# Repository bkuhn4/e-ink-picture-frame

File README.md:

# e-ink-picture-frame

## Getting started

To make it easy for you to get started with GitLab, here's a list of recommended next steps.

Already a pro? Just edit this README.md and make it your own. Want to make it easy? [Use the template at the bottom](#editing-this-readme)!

## Add your files

- [ ] [Create](https://docs.gitlab.com/ee/user/project/repository/web_editor.html#create-a-file) or [upload](https://docs.gitlab.com/ee/user/project/repository/web_editor.html#upload-a-file) files
- [ ] [Add files using the command line](https://docs.gitlab.com/topics/git/add_files/#add-files-to-a-git-repository) or push an existing Git repository with the following command:

```
cd existing_repo
git remote add origin https://git.ece.iastate.edu/etg_dev/cpre_488_pcam.git
git branch -M main
git push -uf origin main
```

## Integrate with your tools

- [ ] [Set up project integrations](https://git.ece.iastate.edu/etg_dev/cpre_488_pcam/-/settings/integrations)

## Collaborate with your team

- [ ] [Invite team members and collaborators](https://docs.gitlab.com/ee/user/project/members/)
- [ ] [Create a new merge request](https://docs.gitlab.com/ee/user/project/merge_requests/creating_merge_requests.html)
- [ ] [Automatically close issues from merge requests](https://docs.gitlab.com/ee/user/project/issues/managing_issues.html#closing-issues-automatically)
- [ ] [Enable merge request approvals](https://docs.gitlab.com/ee/user/project/merge_requests/approvals/)
- [ ] [Set auto-merge](https://docs.gitlab.com/user/project/merge_requests/auto_merge/)

## Test and Deploy

Use the built-in continuous integration in GitLab.

- [ ] [Get started with GitLab CI/CD](https://docs.gitlab.com/ee/ci/quick_start/)
- [ ] [Analyze your code for known vulnerabilities with Static Application Security Testing (SAST)](https://docs.gitlab.com/ee/user/application_security/sast/)
- [ ] [Deploy to Kubernetes, Amazon EC2, or Amazon ECS using Auto Deploy](https://docs.gitlab.com/ee/topics/autodevops/requirements.html)
- [ ] [Use pull-based deployments for improved Kubernetes management](https://docs.gitlab.com/ee/user/clusters/agent/)
- [ ] [Set up protected environments](https://docs.gitlab.com/ee/ci/environments/protected_environments.html)

***

# Editing this README

When you're ready to make this README your own, just edit this file and use the handy template below (or feel free to structure it however you want - this is just a starting point!). Thanks to [makeareadme.com](https://www.makeareadme.com/) for this template.

## Suggestions for a good README

Every project is different, so consider which of these sections apply to yours. The sections used in the template are suggestions for most open source projects. Also keep in mind that while a README can be too long and detailed, too long is better than too short. If you think your README is too long, consider utilizing another form of documentation rather than cutting out information.

## Name
Choose a self-explaining name for your project.

## Description
Let people know what your project can do specifically. Provide context and add a link to any reference visitors might be unfamiliar with. A list of Features or a Background subsection can also be added here. If there are alternatives to your project, this is a good place to list differentiating factors.

## Badges
On some READMEs, you may see small images that convey metadata, such as whether or not all the tests are passing for the project. You can use Shields to add some to your README. Many services also have instructions for adding a badge.

## Visuals
Depending on what you are making, it can be a good idea to include screenshots or even a video (you'll frequently see GIFs rather than actual videos). Tools like ttygif can help, but check out Asciinema for a more sophisticated method.

## Installation
Within a particular ecosystem, there may be a common way of installing things, such as using Yarn, NuGet, or Homebrew. However, consider the possibility that whoever is reading your README is a novice and would like more guidance. Listing specific steps helps remove ambiguity and gets people to using your project as quickly as possible. If it only runs in a specific context like a particular programming language version or operating system or has dependencies that have to be installed manually, also add a Requirements subsection.

## Usage
Use examples liberally, and show the expected output if you can. It's helpful to have inline the smallest example of usage that you can demonstrate, while providing links to more sophisticated examples if they are too long to reasonably include in the README.

## Support
Tell people where they can go to for help. It can be any combination of an issue tracker, a chat room, an email address, etc.

## Roadmap
If you have ideas for releases in the future, it is a good idea to list them in the README.

## Contributing
State if you are open to contributions and what your requirements are for accepting them.

For people who want to make changes to your project, it's helpful to have some documentation on how to get started. Perhaps there is a script that they should run or some environment variables that they need to set. Make these steps explicit. These instructions could also be useful to your future self.

You can also document commands to lint the code or run tests. These steps help to ensure high code quality and reduce the likelihood that the changes inadvertently break something. Having instructions for running tests is especially helpful if it requires external setup, such as starting a Selenium server for testing in a browser.

## Authors and acknowledgment
Show your appreciation to those who have contributed to the project.

## License
For open source projects, say how it is licensed.

## Project status
If you have run out of energy or time for your project, put a note at the top of the README saying that development has slowed down or stopped completely. Someone may choose to fork your project or volunteer to step in as a maintainer or owner, allowing your project to keep going. You can also make an explicit request for maintainers.

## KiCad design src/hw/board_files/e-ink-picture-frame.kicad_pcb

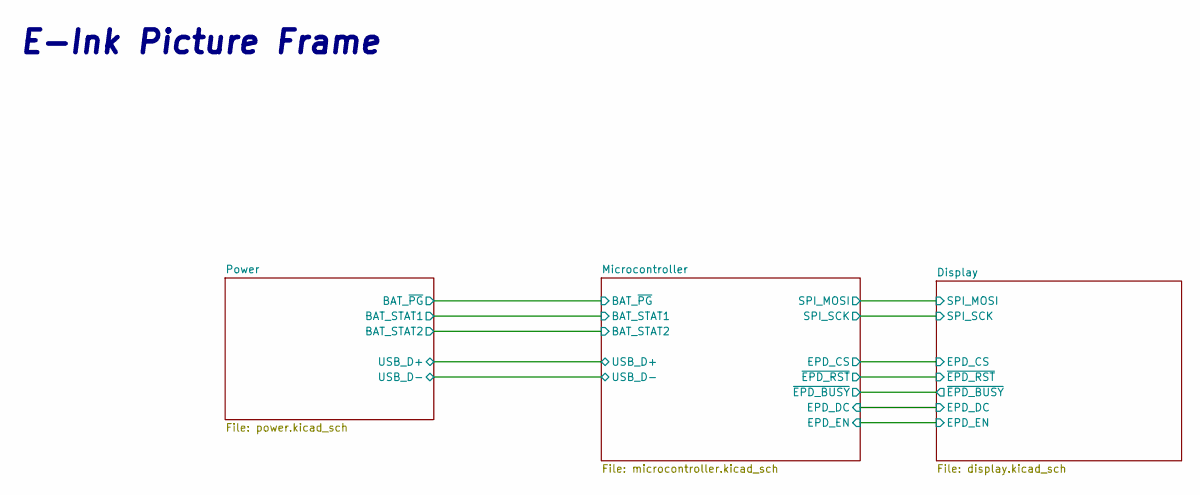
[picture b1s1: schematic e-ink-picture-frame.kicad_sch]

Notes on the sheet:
E-Ink Picture Frame

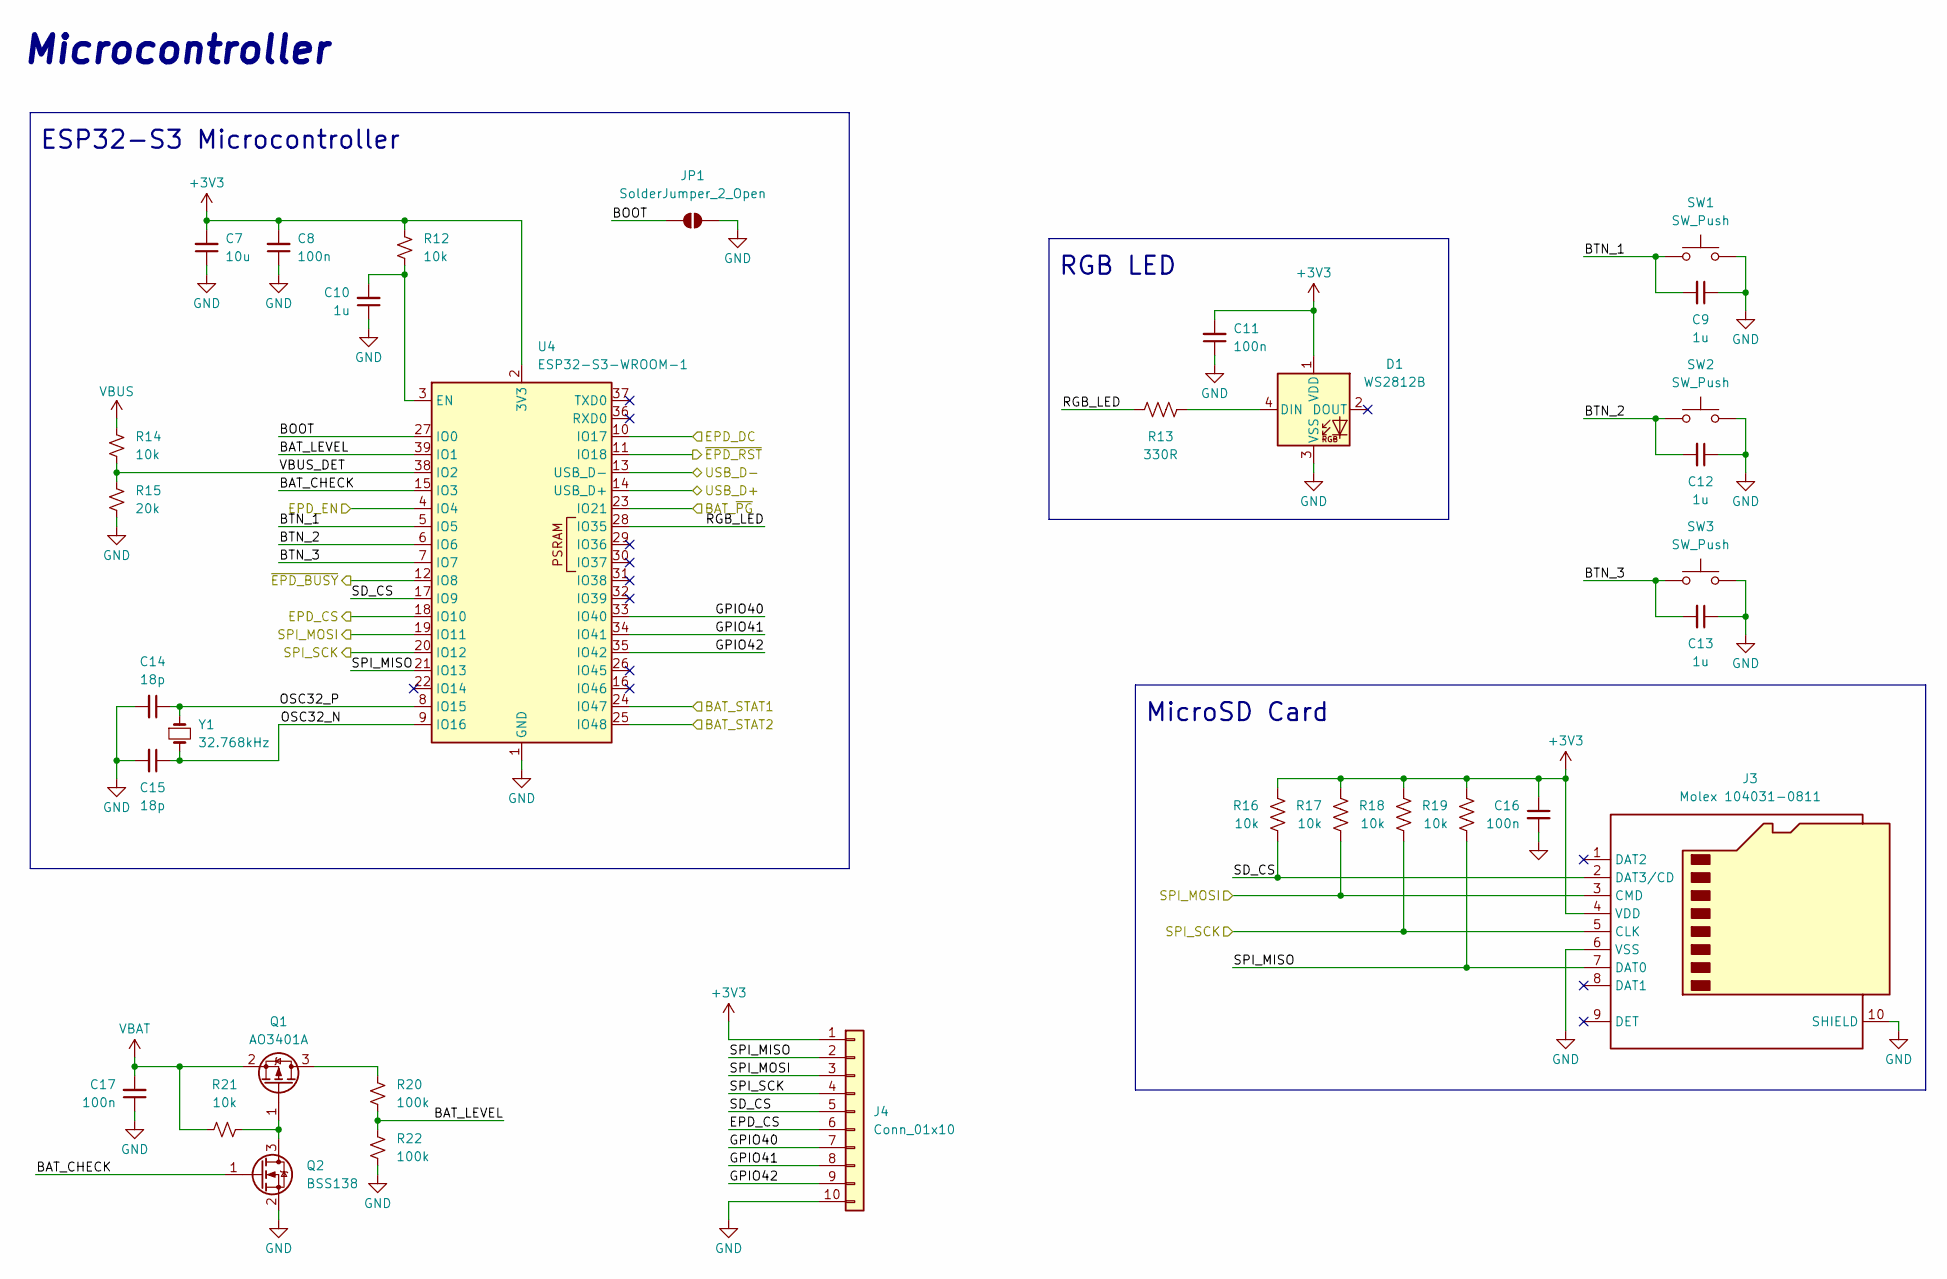
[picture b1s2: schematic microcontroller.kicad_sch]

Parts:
C7: 10u; C_0805_2012Metric_Pad1.18x1.45mm_HandSolder
C8, C11, C16, C17: 100n; C_0603_1608Metric_Pad1.08x0.95mm_HandSolder
C9, C10, C12, C13: 1u; C_0603_1608Metric_Pad1.08x0.95mm_HandSolder
C14, C15: 18p; C_0603_1608Metric_Pad1.08x0.95mm_HandSolder
D1: WS2812B; LED_WS2812B_PLCC4_5.0x5.0mm_P3.2mm
J3: Molex 104031-0811; microSD_HC_Hirose_DM3D-SF
J4: Conn_01x10; PinSocket_1x10_P2.54mm_Horizontal
JP1: SolderJumper_2_Open; SolderJumper-2_P1.3mm_Open_RoundedPad1.0x1.5mm
Q1: AO3401A; SOT-23
Q2: BSS138; SOT-23
R12, R14, R16, R17, R18, R19, R21: 10k; R_0603_1608Metric_Pad0.98x0.95mm_HandSolder
R13: 330R; R_0603_1608Metric_Pad0.98x0.95mm_HandSolder
R15: 20k; R_0603_1608Metric_Pad0.98x0.95mm_HandSolder
R20, R22: 100k; R_0805_2012Metric_Pad1.20x1.40mm_HandSolder
SW1, SW2, SW3: SW_Push; SW_PUSH_6mm
U4: ESP32-S3-WROOM-1
Y1: 32.768kHz; Crystal_SMD_3215-2Pin_3.2x1.5mm

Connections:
+3V3: C7.2, C8.2, C11.2, C16.1, D1.1 (VDD), J3.4 (VDD), J4.1, R12.1, R16.1, R17.1, R18.1, R19.1, U4.2 (3V3); also elsewhere on the board
/Display/EPD_DC: U4.10 (IO17); also elsewhere on the board
/Display/EPD_EN: U4.4 (IO4); also elsewhere on the board
/Display/~EPD_BUSY: U4.12 (IO8); also elsewhere on the board
/Display/~EPD_RST: U4.11 (IO18); also elsewhere on the board
/Microcontroller/BAT_CHECK: Q2.1 (G), U4.15 (IO3)
/Microcontroller/BAT_LEVEL: R20.2, R22.1, U4.39 (IO1)
/Microcontroller/BAT_STAT1: U4.24 (IO47); also elsewhere on the board
/Microcontroller/BAT_STAT2: U4.25 (IO48); also elsewhere on the board
/Microcontroller/BAT_~PG: U4.23 (IO21); also elsewhere on the board
/Microcontroller/BOOT: JP1.1 (A), U4.27 (IO0)
/Microcontroller/BTN_1: C9.2, SW1.1, U4.5 (IO5)
/Microcontroller/BTN_2: C12.2, SW2.1, U4.6 (IO6)
/Microcontroller/BTN_3: C13.2, SW3.1, U4.7 (IO7)
/Microcontroller/EPD_CS: J4.6, U4.18 (IO10); also elsewhere on the board
/Microcontroller/GPIO40: J4.7, U4.33 (IO40)
/Microcontroller/GPIO41: J4.8, U4.34 (IO41)
/Microcontroller/GPIO42: J4.9, U4.35 (IO42)
/Microcontroller/OSC32_N: C15.1, U4.9 (IO16), Y1.2
/Microcontroller/OSC32_P: C14.1, U4.8 (IO15), Y1.1
/Microcontroller/RGB_LED: R13.1, U4.28 (IO35)
/Microcontroller/SD_CS: J3.2 (DAT3/CD), J4.5, R16.2, U4.17 (IO9)
/Microcontroller/SPI_MISO: J3.7 (DAT0), J4.2, R19.2, U4.21 (IO13)
/Microcontroller/SPI_MOSI: J3.3 (CMD), J4.3, R17.2, U4.19 (IO11); also elsewhere on the board
/Microcontroller/SPI_SCK: J3.5 (CLK), J4.4, R18.2, U4.20 (IO12); also elsewhere on the board
/Microcontroller/USB_D+: U4.14 (USB_D+); also elsewhere on the board
/Microcontroller/USB_D-: U4.13 (USB_D-); also elsewhere on the board
/Microcontroller/VBUS_DET: R14.2, R15.1, U4.38 (IO2)
GND: C7.1, C8.1, C9.1, C10.1, C11.1, C12.1, C13.1, C14.2, C15.2, C16.2, C17.1, D1.3 (VSS), J3.6 (VSS), J3.10 (SHIELD), J4.10, JP1.2 (B), Q2.2 (S), R15.2, R22.2, SW1.2, SW2.2, SW3.2, U4.1 (GND), U4.40 (GND), U4.41 (GND); also elsewhere on the board
unnamed: D1.4 (DIN), R13.2
unnamed: Q1.3 (D), R20.1
unnamed: Q1.1 (G), Q2.3 (D), R21.2
unnamed: C10.2, R12.2, U4.3 (EN)
VBAT: C17.2, Q1.2 (S), R21.1; also elsewhere on the board
VBUS: R14.1; also elsewhere on the board

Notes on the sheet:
RGB LED
ESP32-S3 Microcontroller
MicroSD Card
Microcontroller

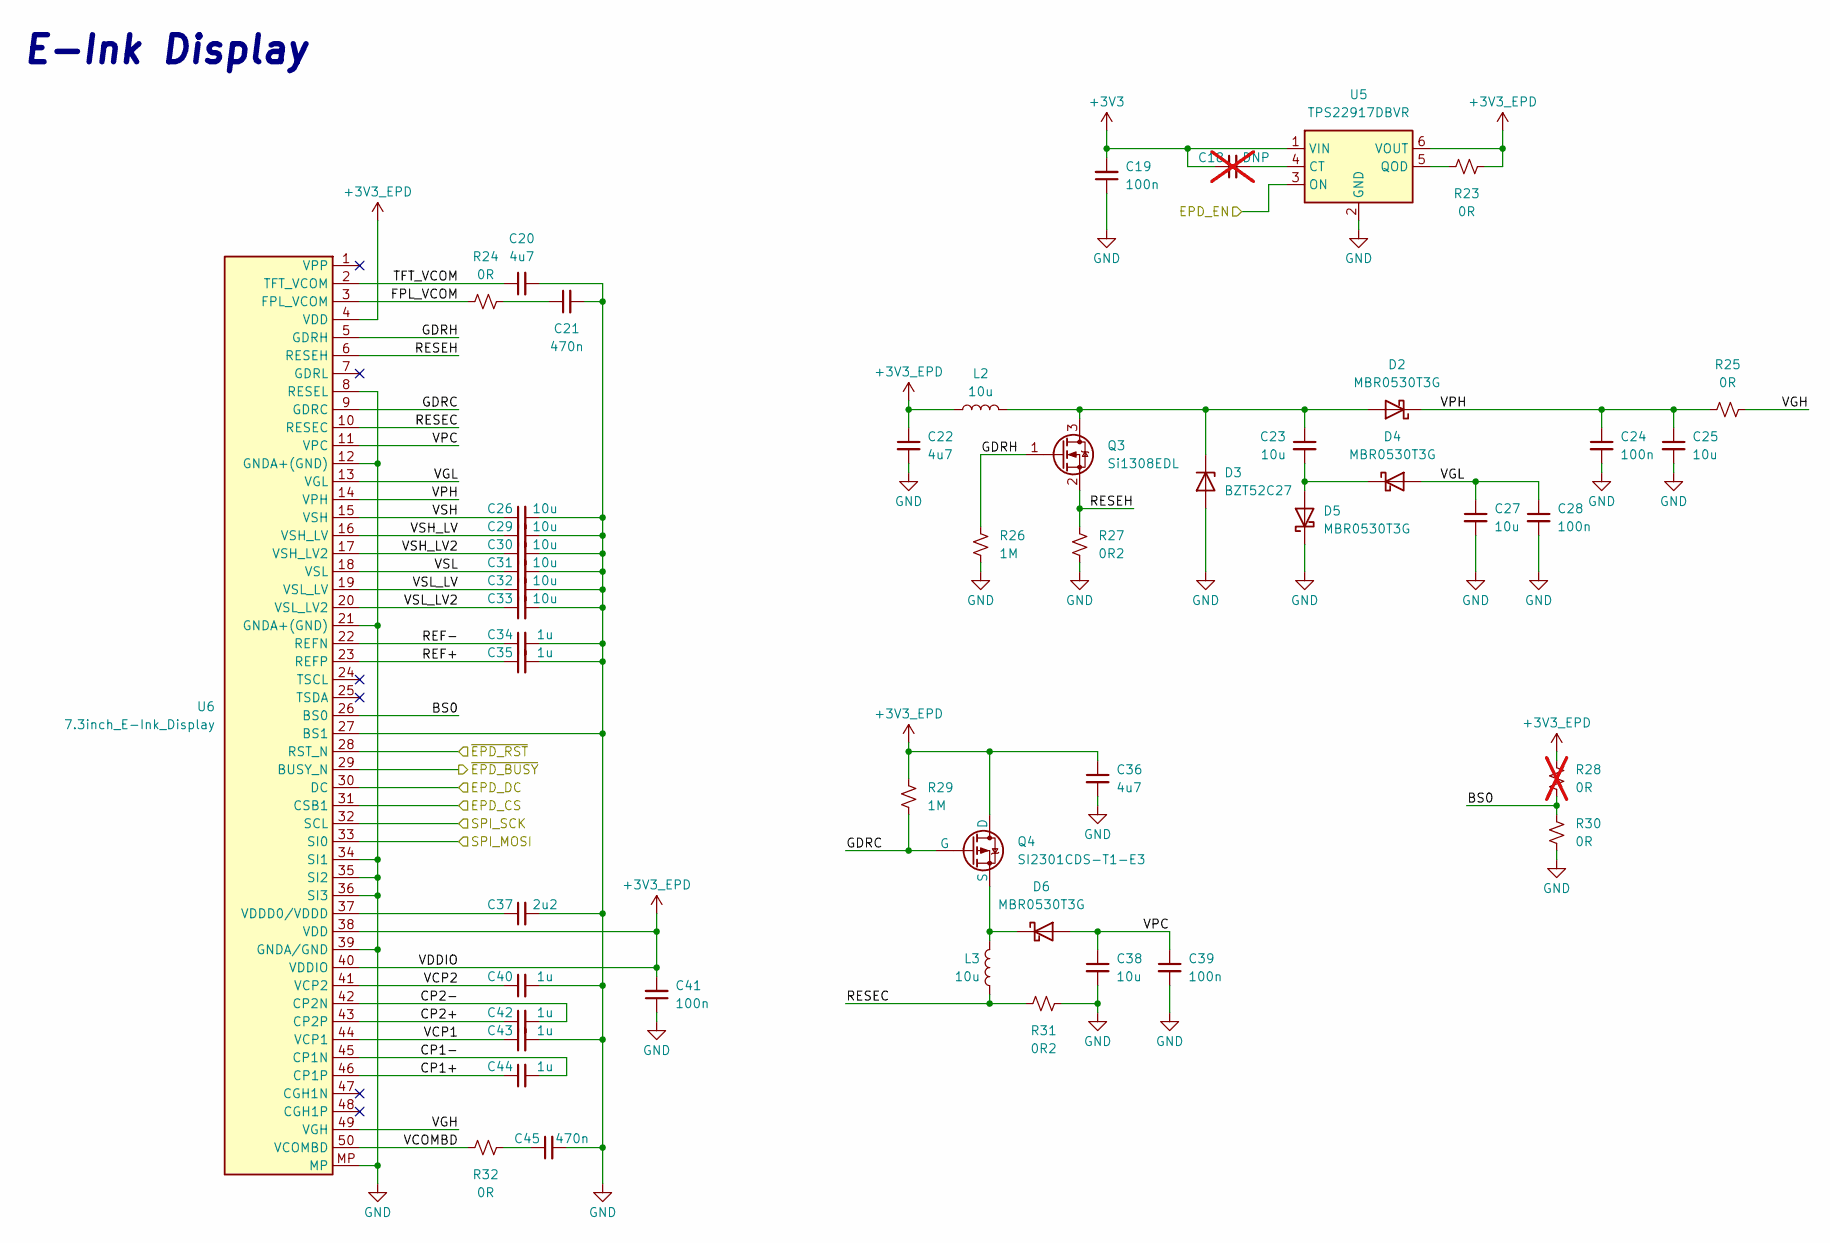
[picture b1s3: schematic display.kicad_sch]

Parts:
C18: DNP; C_0603_1608Metric_Pad1.08x0.95mm_HandSolder; not fitted
C19, C24, C28, C39, C41: 100n; C_0603_1608Metric_Pad1.08x0.95mm_HandSolder
C20, C22, C36: 4u7; C_0805_2012Metric_Pad1.18x1.45mm_HandSolder
C21, C45: 470n; C_0603_1608Metric_Pad1.08x0.95mm_HandSolder
C23, C25, C26, C27, C29, C30, C31, C32, C33, C38: 10u; C_0805_2012Metric_Pad1.18x1.45mm_HandSolder
C34, C35, C40, C42, C43, C44: 1u; C_0603_1608Metric_Pad1.08x0.95mm_HandSolder
C37: 2u2; C_0603_1608Metric_Pad1.08x0.95mm_HandSolder
D2, D4, D5, D6: MBR0530T3G; D_SOD-123
D3: BZT52C27; D_SOD-123F
L2, L3: 10u; L_Bourns_SRN6045TA
Q3: Si1308EDL; SOT-323_SC-70
Q4: SI2301CDS-T1-E3; SOT-23
R23, R24, R25, R30, R32: 0R; R_0603_1608Metric_Pad0.98x0.95mm_HandSolder
R26, R29: 1M; R_0805_2012Metric_Pad1.20x1.40mm_HandSolder
R27, R31: 0R2; R_0603_1608Metric_Pad0.98x0.95mm_HandSolder
R28: 0R; R_0603_1608Metric_Pad0.98x0.95mm_HandSolder; not fitted
U5: TPS22917DBVR; SOT-23-6
U6: 7.3inch_E-Ink_Display; TE_5-1734839-0_1x50-1MP_P0.5mm_Horizontal

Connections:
+3V3: C18.1, C19.2, U5.1 (VIN); also elsewhere on the board
+3V3_EPD: C22.1, C36.1, C41.2, L2.1, Q4.3 (D), R23.1, R28.2, R29.1, U5.6 (VOUT), U6.4 (VDD), U6.38 (VDD), U6.40 (VDDIO)
/Display/BS0: R28.1, R30.2, U6.26 (BS0)
/Display/CP1+: C44.1, U6.46 (CP1P)
/Display/CP1-: C44.2, U6.45 (CP1N)
/Display/CP2+: C42.1, U6.43 (CP2P)
/Display/CP2-: C42.2, U6.42 (CP2N)
/Display/EPD_DC: U6.30 (DC); also elsewhere on the board
/Display/EPD_EN: U5.3 (ON); also elsewhere on the board
/Display/FPL_VCOM: R24.1, U6.3 (FPL_VCOM)
/Display/GDRC: Q4.1 (G), R29.2, U6.9 (GDRC)
/Display/GDRH: Q3.1 (G), R26.1, U6.5 (GDRH)
/Display/REF+: C35.1, U6.23 (REFP)
/Display/REF-: C34.1, U6.22 (REFN)
/Display/RESEC: L3.1, R31.2, U6.10 (RESEC)
/Display/RESEH: Q3.2 (S), R27.2, U6.6 (RESEH)
/Display/TFT_VCOM: C20.1, U6.2 (TFT_VCOM)
/Display/VCOMBD: R32.1, U6.50 (VCOMBD)
/Display/VCP1: C43.1, U6.44 (VCP1)
/Display/VCP2: C40.1, U6.41 (VCP2)
/Display/VGH: R25.2, U6.49 (VGH)
/Display/VGL: C27.1, C28.1, D4.2 (A), U6.13 (VGL)
/Display/VPC: C38.1, C39.1, D6.2 (A), U6.11 (VPC)
/Display/VPH: C24.1, C25.1, D2.1 (K), R25.1, U6.14 (VPH)
/Display/VSH: C26.1, U6.15 (VSH)
/Display/VSH_LV: C29.1, U6.16 (VSH_LV)
/Display/VSH_LV2: C30.1, U6.17 (VSH_LV2)
/Display/VSL: C31.1, U6.18 (VSL)
/Display/VSL_LV: C32.1, U6.19 (VSL_LV)
/Display/VSL_LV2: C33.1, U6.20 (VSL_LV2)
/Display/~EPD_BUSY: U6.29 (BUSY_N); also elsewhere on the board
/Display/~EPD_RST: U6.28 (RST_N); also elsewhere on the board
/Microcontroller/EPD_CS: U6.31 (CSB1); also elsewhere on the board
/Microcontroller/SPI_MOSI: U6.33 (SI0); also elsewhere on the board
/Microcontroller/SPI_SCK: U6.32 (SCL); also elsewhere on the board
GND: C19.1, C20.2, C21.2, C22.2, C24.2, C25.2, C26.2, C27.2, C28.2, C29.2, C30.2, C31.2, C32.2, C33.2, C34.2, C35.2, C36.2, C37.2, C38.2, C39.2, C40.2, C41.1, C43.2, C45.2, D3.2 (A), D5.1 (K), R26.2, R27.1, R30.1, R31.1, U5.2 (GND), U6.8 (RESEL), U6.12 (GNDA+(GND)), U6.21 (GNDA+(GND)), U6.27 (BS1), U6.34 (SI1), U6.35 (SI2), U6.36 (SI3), U6.39 (GNDA/GND), U6.MP; also elsewhere on the board
unnamed: C21.1, R24.2
unnamed: C45.1, R32.2
unnamed: C23.1, D2.2 (A), D3.1 (K), L2.2, Q3.3 (D)
unnamed: C23.2, D4.1 (K), D5.2 (A)
unnamed: D6.1 (K), L3.2, Q4.2 (S)
unnamed: C18.2, U5.4 (CT)
unnamed: R23.2, U5.5 (QOD)
unnamed: C37.1, U6.37 (VDDD0/VDDD)

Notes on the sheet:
E-Ink Display

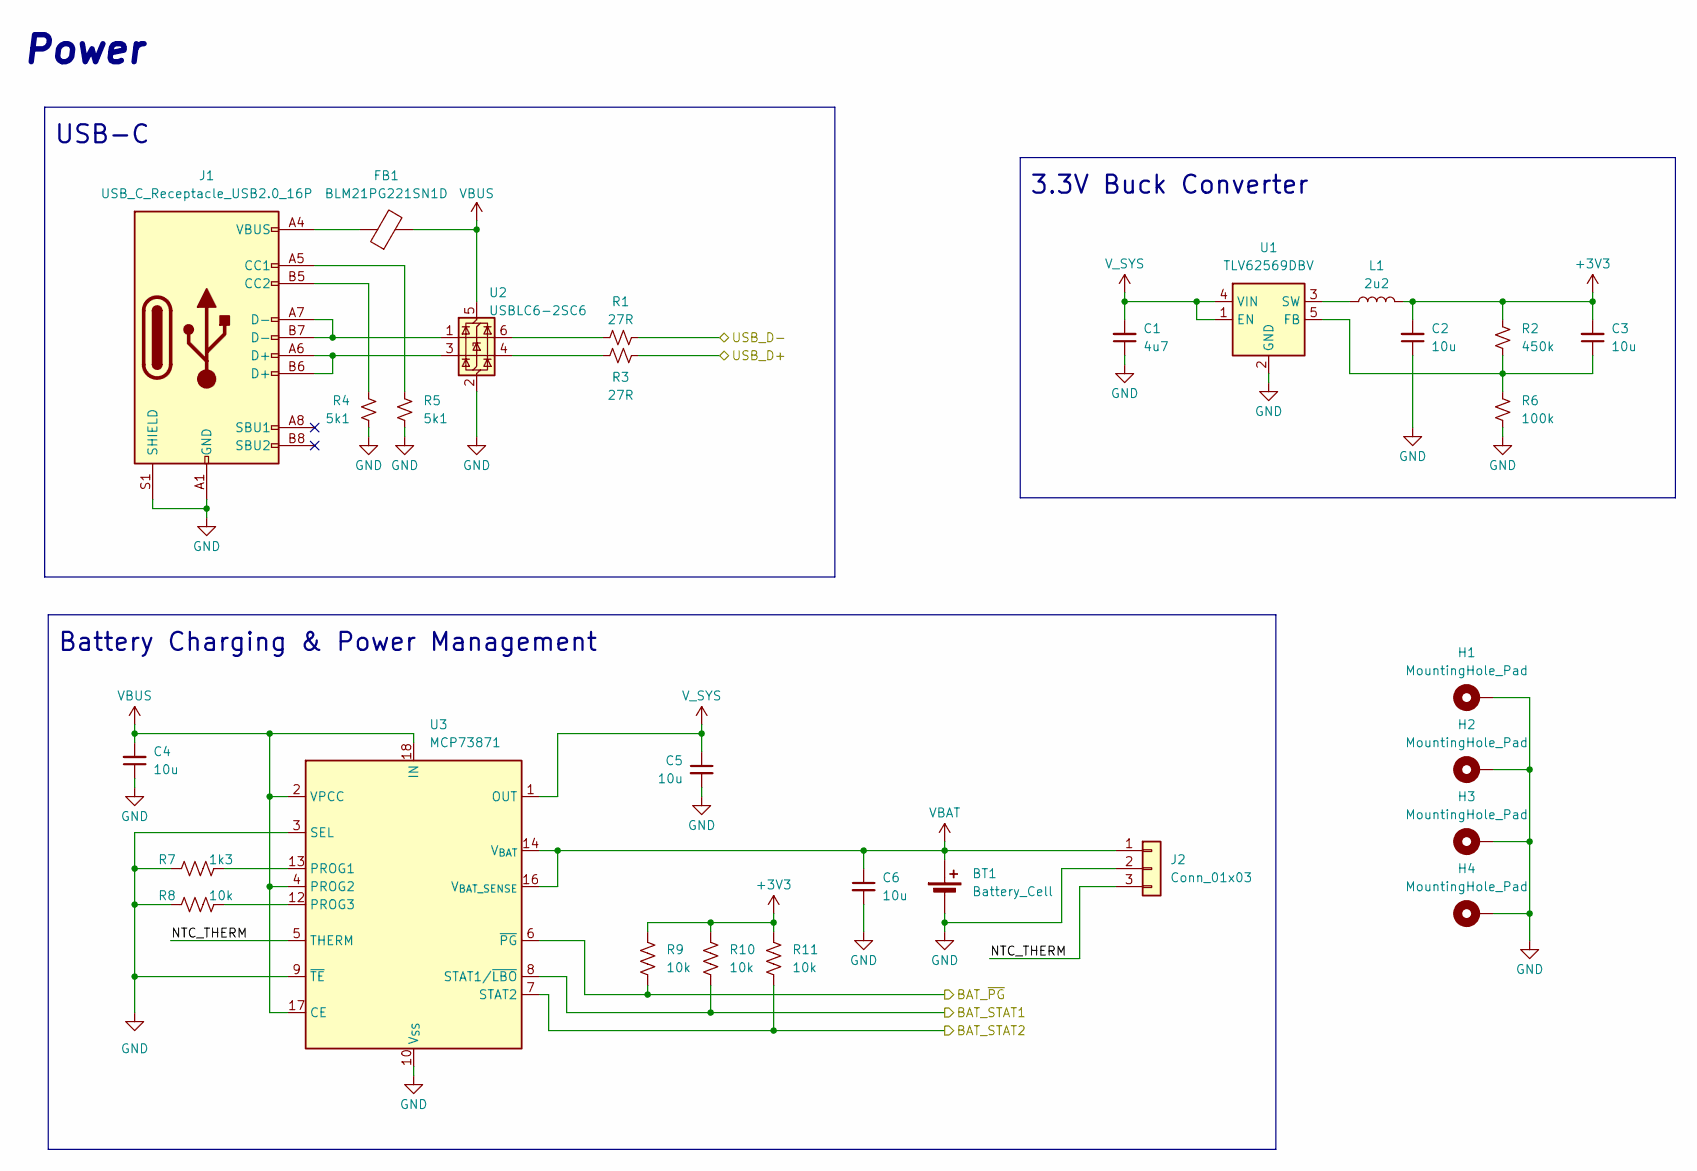
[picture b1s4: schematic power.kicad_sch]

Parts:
BT1: Battery_Cell
C1: 4u7; C_0805_2012Metric_Pad1.18x1.45mm_HandSolder; LCSC C1591
C2, C3, C4: 10u; C_0805_2012Metric_Pad1.18x1.45mm_HandSolder; LCSC C1591
C5, C6: 10u; C_0805_2012Metric_Pad1.18x1.45mm_HandSolder
FB1: BLM21PG221SN1D; L_0805_2012Metric_Pad1.05x1.20mm_HandSolder
H1, H2, H3, H4: MountingHole_Pad; MountingHole_3.2mm_M3_Pad
J1: USB_C_Receptacle_USB2.0_16P; USB_C_Receptacle_GCT_USB4105-xx-A_16P_TopMnt_Horizontal
J2: Conn_01x03; PinSocket_1x03_P2.54mm_Horizontal
L1: 2u2; L_Bourns-SRN4018; MPN SRN4018-2R2M
R1, R3: 27R; R_0603_1608Metric_Pad0.98x0.95mm_HandSolder
R2: 450k; R_0805_2012Metric_Pad1.20x1.40mm_HandSolder
R4, R5: 5k1; R_0603_1608Metric_Pad0.98x0.95mm_HandSolder
R6: 100k; R_0805_2012Metric_Pad1.20x1.40mm_HandSolder
R7: 1k3; R_0603_1608Metric_Pad0.98x0.95mm_HandSolder
R8, R9, R10, R11: 10k; R_0603_1608Metric_Pad0.98x0.95mm_HandSolder
U1: TLV62569DBV; SOT-23-5
U2: USBLC6-2SC6; SOT-23-6
U3: MCP73871; QFN-20-1EP_4x4mm_P0.5mm_EP2.5x2.5mm

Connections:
+3V3: C2.2, C3.2, L1.2, R2.1, R9.2, R10.2, R11.2; also elsewhere on the board
/Microcontroller/BAT_STAT1: R10.1, U3.8 (STAT1/~LBO); also elsewhere on the board
/Microcontroller/BAT_STAT2: R11.1, U3.7 (STAT2); also elsewhere on the board
/Microcontroller/BAT_~PG: R9.1, U3.6 (~PG); also elsewhere on the board
/Microcontroller/USB_D+: R3.1; also elsewhere on the board
/Microcontroller/USB_D-: R1.2; also elsewhere on the board
/Power/NTC_THERM: J2.3, U3.5 (THERM)
GND: BT1.2 (-), C1.1, C2.1, C4.1, C5.2, C6.2, H1.1, H2.1, H3.1, H4.1, J1.A1 (GND), J1.A12 (GND), J1.B1 (GND), J1.B12 (GND), J1.S1 (SHIELD), J2.2, R4.2, R5.2, R6.2, R7.1, R8.1, U1.2 (GND), U2.2 (GND), U3.3 (SEL), U3.9 (~TE), U3.10 (V_{SS}), U3.11 (V_{SS}), U3.21 (V_{SS}); also elsewhere on the board
unnamed: FB1.1, J1.A4 (VBUS), J1.A9 (VBUS), J1.B4 (VBUS), J1.B9 (VBUS)
unnamed: J1.A5 (CC1), R5.1
unnamed: J1.B5 (CC2), R4.1
unnamed: J1.A6 (D+), J1.B6 (D+), U2.3 (I/O2)
unnamed: J1.A7 (D-), J1.B7 (D-), U2.1 (I/O1)
unnamed: R1.1, U2.6 (I/O1)
unnamed: R3.2, U2.4 (I/O2)
unnamed: C3.1, R2.2, R6.1, U1.5 (FB)
unnamed: L1.1, U1.3 (SW)
unnamed: R7.2, U3.13 (PROG1)
unnamed: R8.2, U3.12 (PROG3)
VBAT: BT1.1 (+), C6.1, J2.1, U3.14 (V_{BAT}), U3.15 (V_{BAT}), U3.16 (V_{BAT_SENSE}); also elsewhere on the board
VBUS: C4.2, FB1.2, U2.5 (VBUS), U3.2 (VPCC), U3.4 (PROG2), U3.17 (CE), U3.18 (IN), U3.19 (IN); also elsewhere on the board
V_SYS: C1.2, C5.1, U1.1 (EN), U1.4 (VIN), U3.1 (OUT), U3.20 (OUT)

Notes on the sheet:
USB-C
Battery Charging & Power Management
3.3V Buck Converter
Power

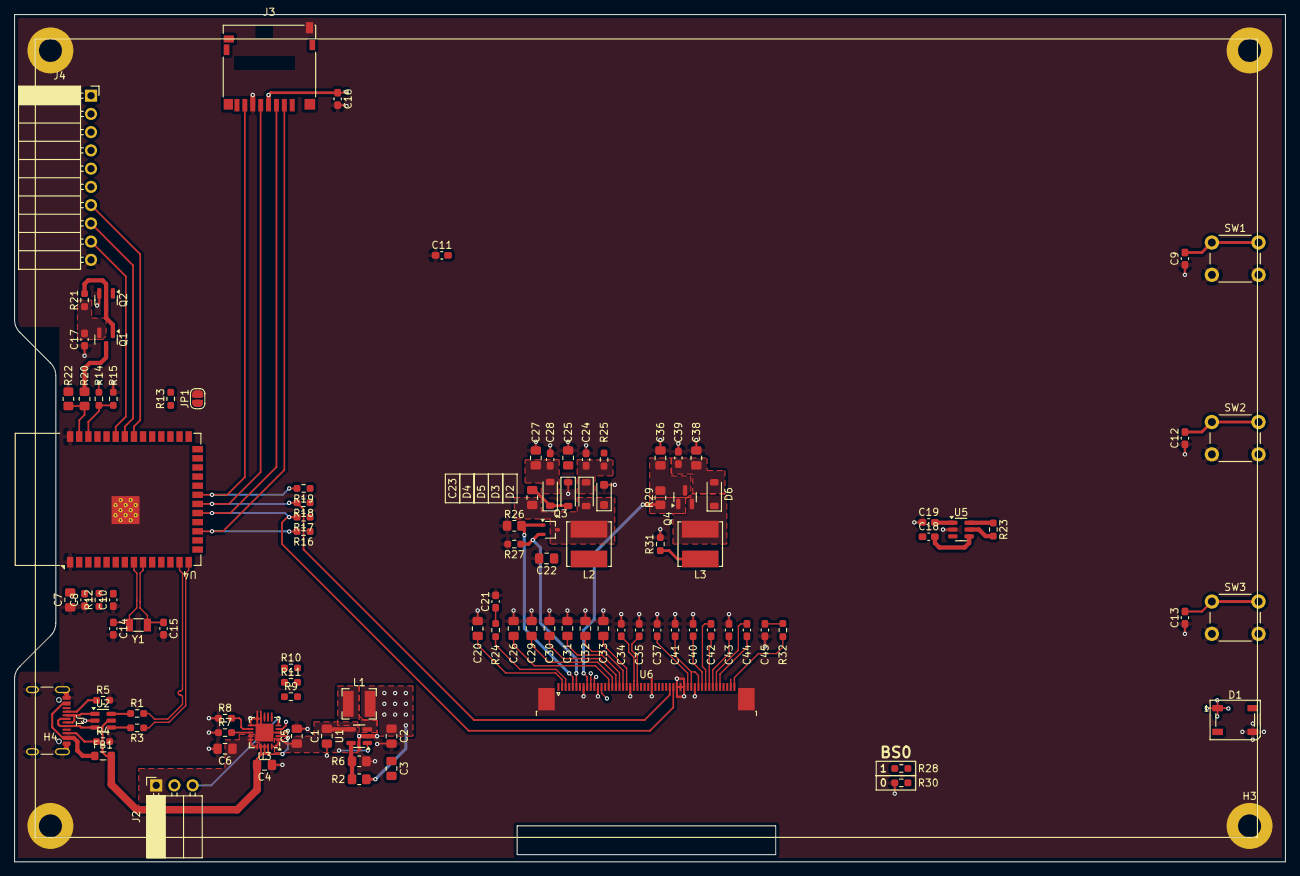
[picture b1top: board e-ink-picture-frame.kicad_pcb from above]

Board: 4 copper layers, 177.0 x 118.0 mm, 110 parts (0 on the bottom side), 83 nets.

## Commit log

2026-03-16 Created Kicad project
2026-03-16 sch progress
2026-04-07 Schematic almost done. Assigning footprints
2026-04-11 Schematic done. Started layout
2026-04-12 Started display circuit layout
2026-04-14 Laid out main components
